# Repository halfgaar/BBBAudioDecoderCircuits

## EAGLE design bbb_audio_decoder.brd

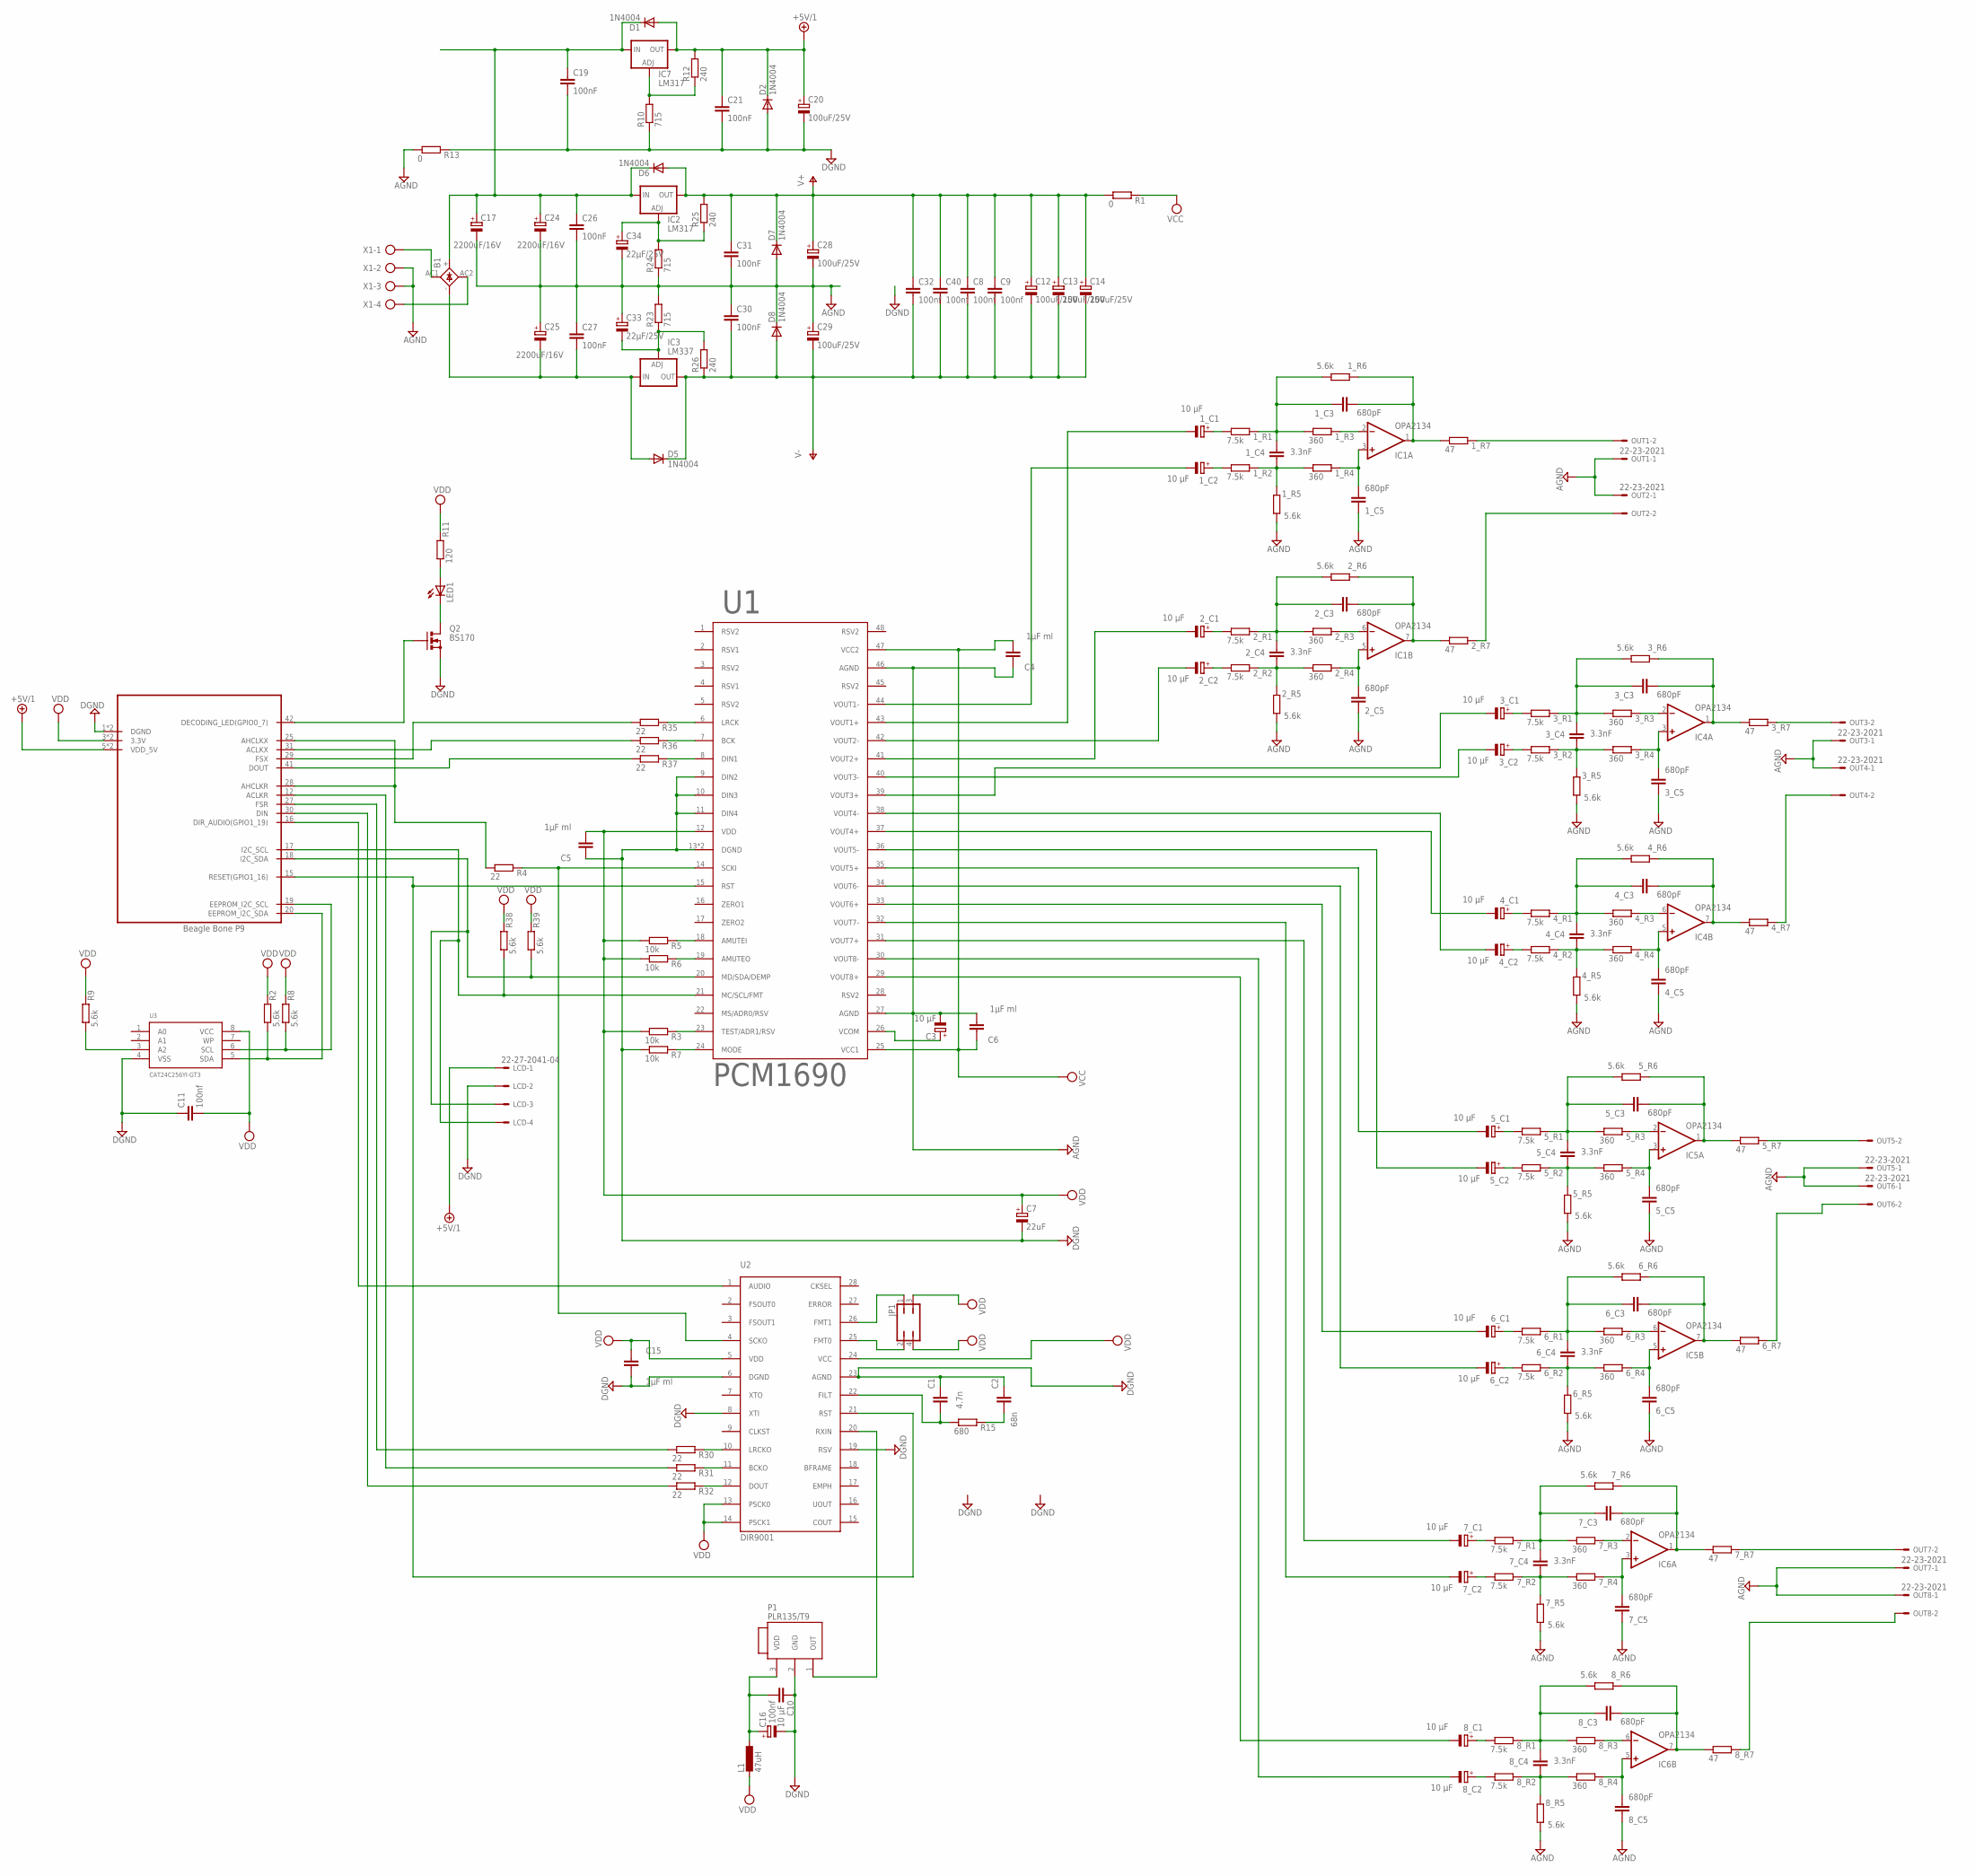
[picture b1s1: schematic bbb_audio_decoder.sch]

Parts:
1_C1, 1_C2, 2_C1, 2_C2, 3_C1, 3_C2, 4_C1, 4_C2, 5_C1, 5_C2, 6_C1, 6_C2, 7_C1, 7_C2, 8_C1, 8_C2: 10 µF; E2-5
1_C3, 1_C5, 2_C3, 2_C5, 3_C3, 3_C5, 4_C3, 4_C5, 5_C3, 5_C5, 6_C3, 6_C5, 7_C3, 7_C5, 8_C3, 8_C5: 680pF; C050-024X044
1_C4, 2_C4, 3_C4, 4_C4, 5_C4, 6_C4, 7_C4, 8_C4: 3.3nF; C050-025X075
1_R1, 1_R2, 2_R1, 2_R2, 3_R1, 3_R2, 4_R1, 4_R2, 5_R1, 5_R2, 6_R1, 6_R2, 7_R1, 7_R2, 8_R1, 8_R2: 7.5k; 0207/7
1_R3, 1_R4, 2_R3, 2_R4, 3_R3, 3_R4, 4_R3, 4_R4, 5_R3, 5_R4, 6_R3, 6_R4, 7_R3, 7_R4, 8_R3, 8_R4: 360; 0207/7
1_R5, 1_R6, 2_R5, 2_R6, 3_R5, 3_R6, 4_R5, 4_R6, 5_R5, 5_R6, 6_R5, 6_R6, 7_R5, 7_R6, 8_R5, 8_R6: 5.6k; 0207/7
1_R7, 2_R7, 3_R7, 4_R7, 5_R7, 6_R7, 7_R7, 8_R7: 47; 0207/7
B1: FB15
C1: 4.7n; C050-024X044
C2: 68n; C050-024X044
C3, C16: 10 µF; E2-5
C4, C5, C6, C15: 1µF ml; C050-024X044
C7: 22uF; E2-5
C8, C9, C10, C11, C32, C40: 100nf; C050-024X044
C12, C13, C14, C20, C28, C29: 100uF/25V; E2,5-6
C17, C24, C25: 2200uF/16V; E5-13
C19, C21, C26, C27, C30, C31: 100nF; C050-024X044
C33, C34: 22µF/25V; E2,5-6
D1, D2, D5, D6, D7, D8: 1N4004; DO41-7.6
IC1, IC4, IC5, IC6: OPA2134; DIL8
IC2, IC7: LM317; 317TS
IC3: LM337; 337TS
JP1: JP2Q
L1: 47uH; 0207/10
LCD: 22-27-2041-04; 6410-04
LED1: LEDSMT1206; 1206
OUT1, OUT2, OUT3, OUT4, OUT5, OUT6, OUT7, OUT8: 22-23-2021
P1: PLR135/T9
Q2: BS170; SOT54E
R1, R13: 0; 0204V
R2, R8, R9, R38, R39: 5.6k; 0207/7
R3, R5, R6, R7: 10k; 0207/7
R4, R30, R31, R32, R35, R36, R37: 22; 0207/7
R10, R23: 715; 0204V
R11: 120; 0204V
R12, R25, R26: 240; 0204V
R15: 680; 0207/7
R24: 715; 0207/10
U1: PCM1690; HTSSOP48DFD
U2: DIR9001; TSSOP28
U3: CAT24C256YI-GT3; TSSOP8
U$1: BEAGLEBONEP9; HEADERS23-2
X1: AK500/4

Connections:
ACLKR: R31.1, U$1.12 (ACLKR)
ACLKX: R36.1, U$1.31 (ACLKX)
AGND: 1_C5.1, 1_R5.1, 2_C5.1, 2_R5.1, 3_C5.1, 3_R5.1, 4_C5.1, 4_R5.1, 5_C5.1, 5_R5.1, 6_C5.1, 6_R5.1, 7_C5.1, 7_R5.1, 8_C5.1, 8_R5.1, C3.-, C4.1, C6.2, C17.-, C24.-, C25.+, C26.2, C27.1, C28.-, C29.+, C30.1, C31.2, C33.+, C34.-, D7.A, D8.C, OUT1.1, OUT2.1, OUT3.1, OUT4.1, OUT5.1, OUT6.1, OUT7.1, OUT8.1, R13.1, R23.2, R24.1, U1.27 (AGND), U1.46 (AGND), X1.2, X1.3
CAPE_I2C_SCL: R8.1, U3.6 (SCL), U$1.19 (EEPROM_I2C_SCL)
CAPE_I2C_SDA: R2.1, U3.5 (SDA), U$1.20 (EEPROM_I2C_SDA)
DGND: C1.1, C2.1, C5.1, C7.-, C10.1, C11.1, C15.2, C16.-, C19.2, C20.-, C21.2, D2.A, LCD.2, P1.2 (GND), Q2.S, R7.1, R10.1, R13.2, U1.9 (DIN2), U1.10 (DIN3), U1.11 (DIN4), U1.13 (DGND), U1.EXP (DGND), U2.6 (DGND), U2.8 (XTI), U2.19 (RSV), U2.23 (AGND), U3.4 (VSS), U$1.1 (DGND), U$1.2 (DGND)
DIN: R32.1, U$1.30 (DIN)
DIR_AUDIO: U2.1 (AUDIO), U$1.16 (DIR_AUDIO(GPIO1_19))
DOUT: R37.1, U$1.41 (DOUT)
FILT: C1.2, R15.1, U2.22 (FILT)
FSR: R30.1, U$1.27 (FSR)
FSX: R35.1, U$1.29 (FSX)
MCLK: R4.1, U$1.25 (AHCLKX), U$1.28 (AHCLKR)
unnamed: B1.AC2, X1.4
unnamed: R3.2, U1.23 (TEST/ADR1/RSV)
unnamed: B1.AC1, X1.1
unnamed: LED1.A, R11.1
unnamed: R4.2, U1.14 (SCKI), U2.4 (SCKO)
unnamed: C2.2, R15.2
unnamed: JP1.2, U2.25 (FMT0)
unnamed: JP1.1, U2.26 (FMT1)
unnamed: 3_C4.1, 3_R2.2, 3_R4.1, 3_R5.2
unnamed: 3_C3.1, 3_C4.2, 3_R1.2, 3_R3.1, 3_R6.1
unnamed: R5.2, U1.18 (AMUTEI)
unnamed: C10.2, C16.+, L1.1, P1.3 (VDD)
unnamed: 1_C4.1, 1_R2.2, 1_R4.1, 1_R5.2
unnamed: 2_C4.1, 2_R2.2, 2_R4.1, 2_R5.2
unnamed: 2_C3.1, 2_C4.2, 2_R1.2, 2_R3.1, 2_R6.1
unnamed: 3_C5.2, 3_R4.2, IC4.3 (+IN)
unnamed: R6.2, U1.19 (AMUTEO)
unnamed: 1_C3.1, 1_C4.2, 1_R1.2, 1_R3.1, 1_R6.1
unnamed: R7.2, U1.24 (MODE)
unnamed: P1.1 (OUT), U2.20 (RXIN)
unnamed: 3_C3.2, 3_R6.2, 3_R7.1, IC4.1 (OUT)
unnamed: 3_R3.2, IC4.2 (-IN)
unnamed: 1_R3.2, IC1.2 (-IN)
unnamed: 1_C5.2, 1_R4.2, IC1.3 (+IN)
unnamed: 1_C2.+, 1_R2.1
unnamed: 1_C3.2, 1_R6.2, 1_R7.1, IC1.1 (OUT)
unnamed: 1_C1.+, 1_R1.1
unnamed: LED1.C, Q2.D
unnamed: 7_C4.1, 7_R2.2, 7_R4.1, 7_R5.2
unnamed: 2_C5.2, 2_R4.2, IC1.5 (+IN)
unnamed: 2_C3.2, 2_R6.2, 2_R7.1, IC1.7 (OUT)
unnamed: 2_R3.2, IC1.6 (-IN)
unnamed: 2_C2.+, 2_R2.1
unnamed: 2_C1.+, 2_R1.1
unnamed: 7_C3.1, 7_C4.2, 7_R1.2, 7_R3.1, 7_R6.1
unnamed: 7_C5.2, 7_R4.2, IC6.3 (+IN)
unnamed: 1_R7.2, OUT1.2
unnamed: 2_R7.2, OUT2.2
unnamed: B1.+, C17.+, C19.1, C24.+, C26.1, D1.C, D6.C, IC2.3 (IN), IC7.3 (IN)
unnamed: IC7.1 (ADJ), R10.2, R12.1
unnamed: B1.-, C25.-, C27.2, D5.A, IC3.2 (IN)
unnamed: C33.-, IC3.1 (ADJ), R23.1, R26.2
unnamed: C34.+, IC2.1 (ADJ), R24.2, R25.1
unnamed: 3_C2.+, 3_R2.1
unnamed: 3_C1.+, 3_R1.1
unnamed: 7_C3.2, 7_R6.2, 7_R7.1, IC6.1 (OUT)
unnamed: 7_R3.2, IC6.2 (-IN)
unnamed: 4_C4.1, 4_R2.2, 4_R4.1, 4_R5.2
unnamed: 4_C3.1, 4_C4.2, 4_R1.2, 4_R3.1, 4_R6.1
unnamed: 4_C5.2, 4_R4.2, IC4.5 (+IN)
unnamed: R32.2, U2.12 (DOUT)
unnamed: R31.2, U2.11 (BCKO)
unnamed: R30.2, U2.10 (LRCKO)
unnamed: R9.1, U3.3 (A2)
unnamed: 4_C3.2, 4_R6.2, 4_R7.1, IC4.7 (OUT)
unnamed: 4_R3.2, IC4.6 (-IN)
unnamed: 4_C2.+, 4_R2.1
unnamed: 4_C1.+, 4_R1.1
unnamed: 7_C2.+, 7_R2.1
unnamed: 7_C1.+, 7_R1.1
unnamed: R37.2, U1.8 (DIN1)
unnamed: R36.2, U1.7 (BCK)
unnamed: R35.2, U1.6 (LRCK)
unnamed: 3_R7.2, OUT3.2
unnamed: 4_R7.2, OUT4.2
unnamed: 5_C4.1, 5_R2.2, 5_R4.1, 5_R5.2
unnamed: 5_C3.1, 5_C4.2, 5_R1.2, 5_R3.1, 5_R6.1
unnamed: 5_C5.2, 5_R4.2, IC5.3 (+IN)
unnamed: 5_C3.2, 5_R6.2, 5_R7.1, IC5.1 (OUT)
unnamed: 5_R3.2, IC5.2 (-IN)
unnamed: 5_C2.+, 5_R2.1
unnamed: 5_C1.+, 5_R1.1
unnamed: 8_C4.1, 8_R2.2, 8_R4.1, 8_R5.2
unnamed: 8_C3.1, 8_C4.2, 8_R1.2, 8_R3.1, 8_R6.1
unnamed: 6_C4.1, 6_R2.2, 6_R4.1, 6_R5.2
unnamed: 6_C3.1, 6_C4.2, 6_R1.2, 6_R3.1, 6_R6.1
unnamed: 6_C5.2, 6_R4.2, IC5.5 (+IN)
unnamed: 6_C3.2, 6_R6.2, 6_R7.1, IC5.7 (OUT)
unnamed: 6_R3.2, IC5.6 (-IN)
unnamed: 6_C2.+, 6_R2.1
unnamed: 6_C1.+, 6_R1.1
unnamed: 5_R7.2, OUT5.2
unnamed: 6_R7.2, OUT6.2
unnamed: 8_C5.2, 8_R4.2, IC6.5 (+IN)
unnamed: 8_C3.2, 8_R6.2, 8_R7.1, IC6.7 (OUT)
unnamed: 8_R3.2, IC6.6 (-IN)
unnamed: 8_C2.+, 8_R2.1
unnamed: 8_C1.+, 8_R1.1
unnamed: 7_R7.2, OUT7.2
unnamed: 8_R7.2, OUT8.2
unnamed: Q2.G, U$1.42 (DECODING_LED(GPIO0_7))
RST: U1.15 (RST), U2.21 (RST), U$1.15 (RESET(GPIO1_16))
SCL: LCD.4, R38.1, U1.21 (MC/SCL/FMT), U$1.17 (I2C_SCL)
SDA: LCD.3, R39.1, U1.20 (MD/SDA/DEMP), U$1.18 (I2C_SDA)
V+: C8.1, C9.1, C12.+, C13.+, C14.+, C28.+, C31.1, C32.1, C40.1, D6.A, D7.C, IC1.8 (V+), IC2.2 (OUT), IC4.8 (V+), IC5.8 (V+), IC6.8 (V+), R1.1, R25.2
V-: C8.2, C9.2, C12.-, C13.-, C14.-, C29.-, C30.2, C32.2, C40.2, D5.C, D8.A, IC1.4 (V-), IC3.3 (OUT), IC4.4 (V-), IC5.4 (V-), IC6.4 (V-), R26.1
VCC: C4.2, C6.1, R1.2, U1.25 (VCC1), U1.47 (VCC2)
VCOM: C3.+, U1.26 (VCOM)
VDD: C5.2, C7.+, C11.2, C15.1, JP1.3, JP1.4, L1.2, R2.2, R3.1, R5.1, R6.1, R8.2, R9.2, R11.2, R38.2, R39.2, U1.12 (VDD), U2.5 (VDD), U2.13 (PSCK0), U2.14 (PSCK1), U2.24 (VCC), U3.8 (VCC), U$1.3 (3.3V), U$1.4 (3.3V)
VDD_5V: C20.+, C21.1, D1.A, D2.C, IC7.2 (OUT), LCD.1, R12.2, U$1.5 (VDD_5V), U$1.6 (VDD_5V)
VOUT1+: 1_C1.-, U1.43 (VOUT1+)
VOUT1-: 1_C2.-, U1.44 (VOUT1-)
VOUT2+: 2_C1.-, U1.41 (VOUT2+)
VOUT2-: 2_C2.-, U1.42 (VOUT2-)
VOUT3+: 3_C1.-, U1.39 (VOUT3+)
VOUT3-: 3_C2.-, U1.40 (VOUT3-)
VOUT4+: 4_C1.-, U1.37 (VOUT4+)
VOUT4-: 4_C2.-, U1.38 (VOUT4-)
VOUT5+: 5_C1.-, U1.35 (VOUT5+)
VOUT5-: 5_C2.-, U1.36 (VOUT5-)
VOUT6+: 6_C1.-, U1.33 (VOUT6+)
VOUT6-: 6_C2.-, U1.34 (VOUT6-)
VOUT7+: 7_C1.-, U1.31 (VOUT7+)
VOUT7-: 7_C2.-, U1.32 (VOUT7-)
VOUT8+: 8_C1.-, U1.29 (VOUT8+)
VOUT8-: 8_C2.-, U1.30 (VOUT8-)

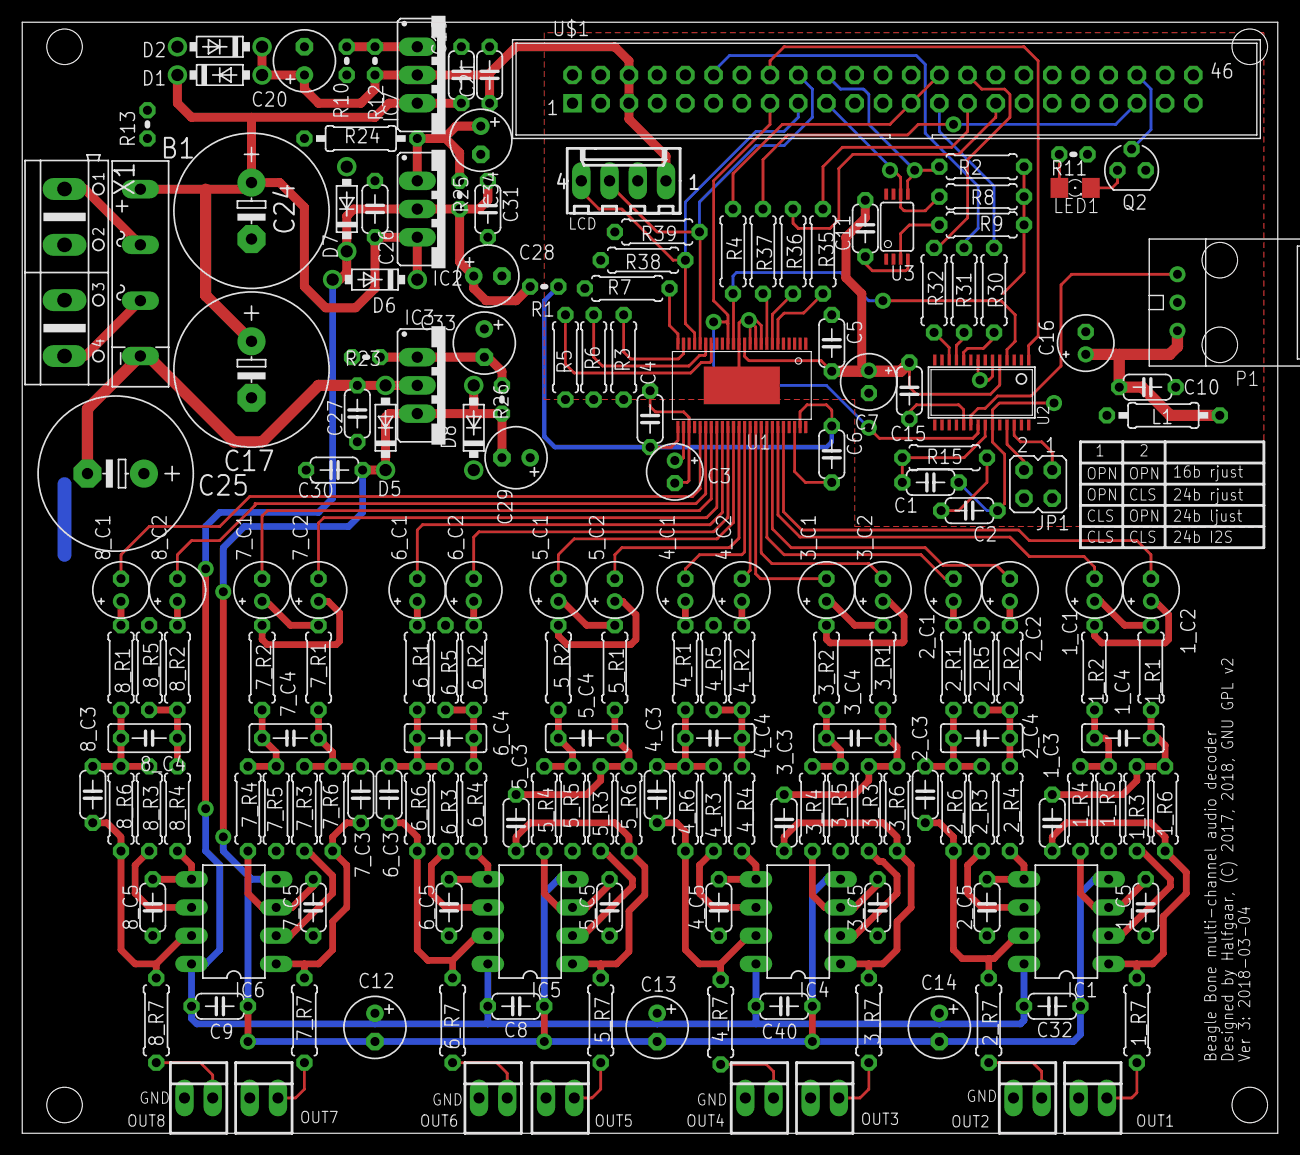
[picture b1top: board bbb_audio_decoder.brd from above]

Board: 2 copper layers, 113.0 x 100.0 mm, 187 parts (0 on the bottom side), 129 nets.

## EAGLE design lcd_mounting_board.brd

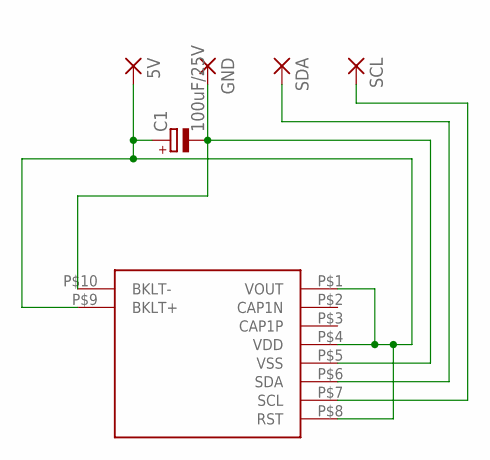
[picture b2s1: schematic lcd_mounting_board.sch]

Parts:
5V: 2,15/1,0
C1: 100uF/25V; E2,5-6
GND: 2,15/1,0
SCL: 2,15/1,0
SDA: 2,15/1,0
U$1: MCCOG22005A6W-BNMLWI

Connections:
5V: 5V.1, C1.+, U$1.P$1 (VOUT), U$1.P$4 (VDD), U$1.P$8 (RST), U$1.P$9 (BKLT+)
GND: C1.-, GND.1, U$1.P$5 (VSS), U$1.P$10 (BKLT-)
SCL: SCL.1, U$1.P$7 (SCL)
SDA: SDA.1, U$1.P$6 (SDA)

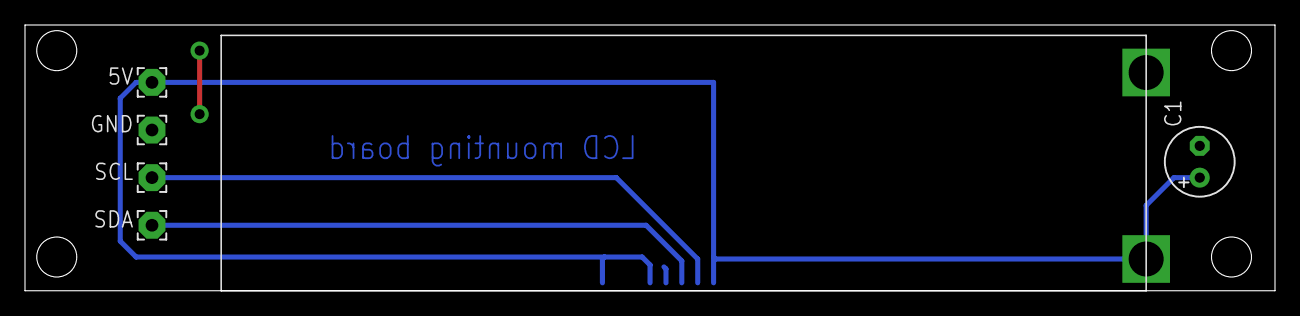
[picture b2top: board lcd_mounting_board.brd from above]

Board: 2 copper layers, 100.0 x 21.3 mm, 6 parts (0 on the bottom side), 4 nets.

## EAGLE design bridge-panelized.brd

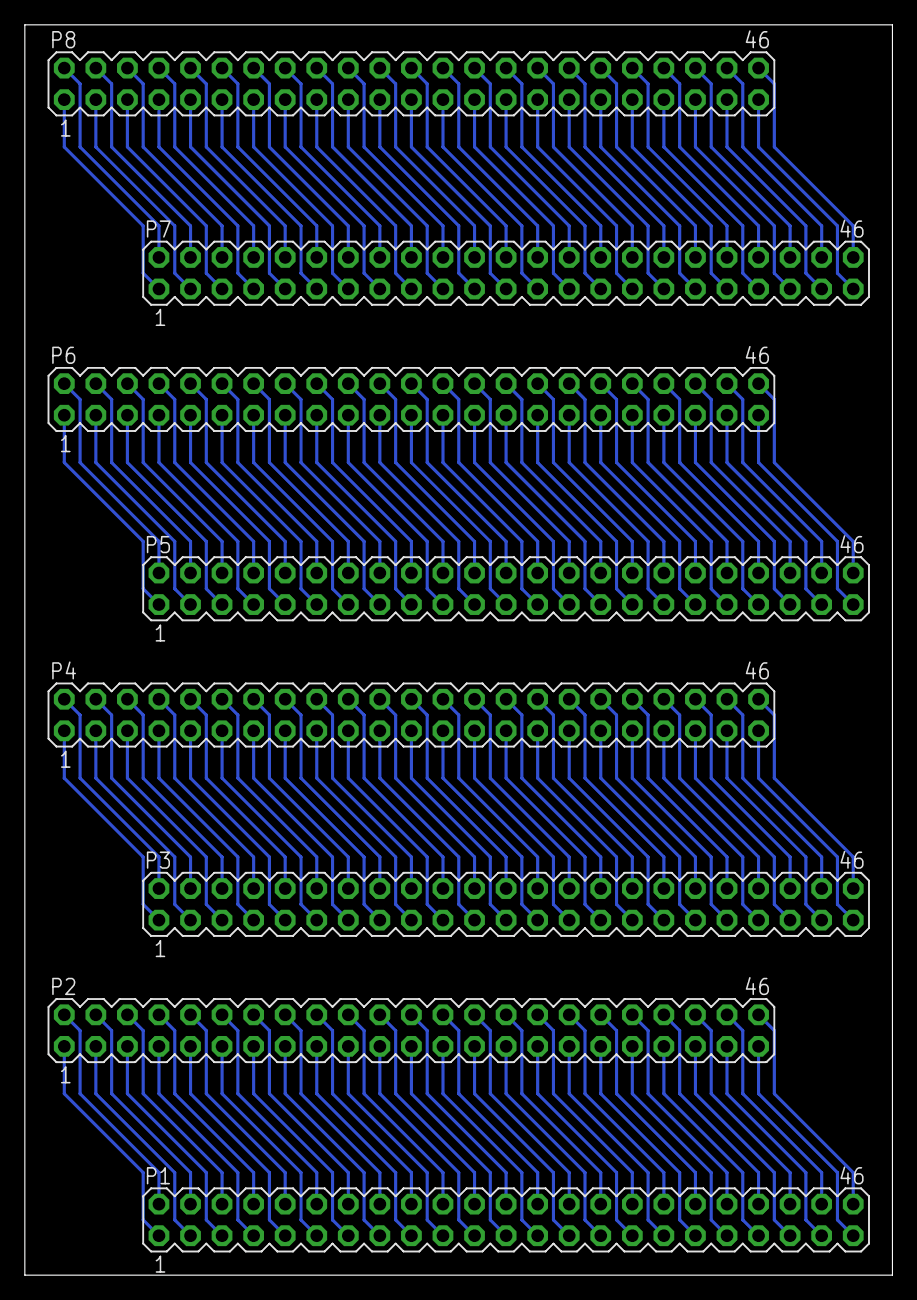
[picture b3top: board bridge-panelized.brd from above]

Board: 2 copper layers, 69.8 x 100.6 mm, 8 parts (0 on the bottom side), 184 nets.

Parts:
P1, P2, P3, P4, P5, P6, P7, P8: HEADERS23-2; MA23-2

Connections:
unnamed: P1.1, P2.1
unnamed: P1.3, P2.3
unnamed: P1.5, P2.5
unnamed: P1.7, P2.7
unnamed: P1.9, P2.9
unnamed: P1.11, P2.11
unnamed: P1.13, P2.13
unnamed: P1.15, P2.15
unnamed: P1.17, P2.17
unnamed: P1.19, P2.19
unnamed: P1.21, P2.21
unnamed: P1.23, P2.23
unnamed: P1.25, P2.25
unnamed: P1.27, P2.27
unnamed: P1.29, P2.29
unnamed: P1.31, P2.31
unnamed: P1.33, P2.33
unnamed: P1.35, P2.35
unnamed: P1.37, P2.37
unnamed: P1.39, P2.39
unnamed: P1.41, P2.41
unnamed: P1.43, P2.43
unnamed: P1.45, P2.45
unnamed: P1.2, P2.2
unnamed: P1.4, P2.4
unnamed: P1.6, P2.6
unnamed: P1.8, P2.8
unnamed: P1.10, P2.10
unnamed: P1.12, P2.12
unnamed: P1.14, P2.14
unnamed: P1.16, P2.16
unnamed: P1.18, P2.18
unnamed: P1.20, P2.20
unnamed: P1.22, P2.22
unnamed: P1.24, P2.24
unnamed: P1.26, P2.26
unnamed: P1.28, P2.28
unnamed: P1.30, P2.30
unnamed: P1.32, P2.32
unnamed: P1.34, P2.34
unnamed: P1.36, P2.36
unnamed: P1.38, P2.38
unnamed: P1.40, P2.40
unnamed: P1.42, P2.42
unnamed: P1.44, P2.44
unnamed: P1.46, P2.46
unnamed: P3.1, P4.1
unnamed: P3.3, P4.3
unnamed: P3.5, P4.5
unnamed: P3.7, P4.7
unnamed: P3.9, P4.9
unnamed: P3.11, P4.11
unnamed: P3.13, P4.13
unnamed: P3.15, P4.15
unnamed: P3.17, P4.17
unnamed: P3.19, P4.19
unnamed: P3.21, P4.21
unnamed: P3.23, P4.23
unnamed: P3.25, P4.25
unnamed: P3.27, P4.27
unnamed: P3.29, P4.29
unnamed: P3.31, P4.31
unnamed: P3.33, P4.33
unnamed: P3.35, P4.35
unnamed: P3.37, P4.37
unnamed: P3.39, P4.39
unnamed: P3.41, P4.41
unnamed: P3.43, P4.43
unnamed: P3.45, P4.45
unnamed: P3.2, P4.2
unnamed: P3.4, P4.4
unnamed: P3.6, P4.6
unnamed: P3.8, P4.8
unnamed: P3.10, P4.10
unnamed: P3.12, P4.12
unnamed: P3.14, P4.14
unnamed: P3.16, P4.16
unnamed: P3.18, P4.18
unnamed: P3.20, P4.20
unnamed: P3.22, P4.22
unnamed: P3.24, P4.24
unnamed: P3.26, P4.26
unnamed: P3.28, P4.28
unnamed: P3.30, P4.30
unnamed: P3.32, P4.32
unnamed: P3.34, P4.34
unnamed: P3.36, P4.36
unnamed: P3.38, P4.38
unnamed: P3.40, P4.40
unnamed: P3.42, P4.42
unnamed: P3.44, P4.44
unnamed: P3.46, P4.46
unnamed: P5.1, P6.1
unnamed: P5.3, P6.3
unnamed: P5.5, P6.5
unnamed: P5.7, P6.7
unnamed: P5.9, P6.9
unnamed: P5.11, P6.11
unnamed: P5.13, P6.13
unnamed: P5.15, P6.15
unnamed: P5.17, P6.17
unnamed: P5.19, P6.19
unnamed: P5.21, P6.21
unnamed: P5.23, P6.23
unnamed: P5.25, P6.25
unnamed: P5.27, P6.27
unnamed: P5.29, P6.29
unnamed: P5.31, P6.31
unnamed: P5.33, P6.33
unnamed: P5.35, P6.35
unnamed: P5.37, P6.37
unnamed: P5.39, P6.39
unnamed: P5.41, P6.41
unnamed: P5.43, P6.43
unnamed: P5.45, P6.45
unnamed: P5.2, P6.2
unnamed: P5.4, P6.4
unnamed: P5.6, P6.6
unnamed: P5.8, P6.8
unnamed: P5.10, P6.10
unnamed: P5.12, P6.12
unnamed: P5.14, P6.14
unnamed: P5.16, P6.16
unnamed: P5.18, P6.18
unnamed: P5.20, P6.20
unnamed: P5.22, P6.22
unnamed: P5.24, P6.24
unnamed: P5.26, P6.26
unnamed: P5.28, P6.28
unnamed: P5.30, P6.30
unnamed: P5.32, P6.32
unnamed: P5.34, P6.34
unnamed: P5.36, P6.36
unnamed: P5.38, P6.38
unnamed: P5.40, P6.40
unnamed: P5.42, P6.42
unnamed: P5.44, P6.44
unnamed: P5.46, P6.46
unnamed: P7.1, P8.1
unnamed: P7.3, P8.3
unnamed: P7.5, P8.5
unnamed: P7.7, P8.7
unnamed: P7.9, P8.9
unnamed: P7.11, P8.11
unnamed: P7.13, P8.13
unnamed: P7.15, P8.15
unnamed: P7.17, P8.17
unnamed: P7.19, P8.19
unnamed: P7.21, P8.21
unnamed: P7.23, P8.23
unnamed: P7.25, P8.25
unnamed: P7.27, P8.27
unnamed: P7.29, P8.29
unnamed: P7.31, P8.31
unnamed: P7.33, P8.33
unnamed: P7.35, P8.35
unnamed: P7.37, P8.37
unnamed: P7.39, P8.39
unnamed: P7.41, P8.41
unnamed: P7.43, P8.43
unnamed: P7.45, P8.45
unnamed: P7.2, P8.2
unnamed: P7.4, P8.4
unnamed: P7.6, P8.6
unnamed: P7.8, P8.8
unnamed: P7.10, P8.10
unnamed: P7.12, P8.12
unnamed: P7.14, P8.14
unnamed: P7.16, P8.16
unnamed: P7.18, P8.18
unnamed: P7.20, P8.20
unnamed: P7.22, P8.22
unnamed: P7.24, P8.24
unnamed: P7.26, P8.26
unnamed: P7.28, P8.28
unnamed: P7.30, P8.30
unnamed: P7.32, P8.32
unnamed: P7.34, P8.34
unnamed: P7.36, P8.36
unnamed: P7.38, P8.38
unnamed: P7.40, P8.40
unnamed: P7.42, P8.42
unnamed: P7.44, P8.44
unnamed: P7.46, P8.46

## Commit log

2015-06-04 Progressing nicely. Time for a first commit.
2017-01-01 Ignores
2017-01-16 Taking the Beaglebone approach
2017-01-22 Reversed opamp
    Because signals are now on top layer, the layout had to be mirrored.
2017-01-22 Copied two extra output stages
2017-01-22 Added another analog output stage
2017-01-22 Added the last analog output stage
2017-01-27 Working on EEPROM and TOSLINK
2017-01-28 Mostly the analog section, routing and squeezing
2017-01-29 Rotated PSU section, and more work since
2017-01-30 stuff
2017-02-02 ignore file
2017-02-02 Very nearly done
    I added some power and ground planes and finished more routing.
    Still a bit of decision making to do before I can finish it.
2017-02-02 Fixed 5mm caps, fixed DRC errors
2017-02-06 Added bridge
2017-02-06 Added screw holes
2017-02-06 Some moving around for DRC and one tiny airwire
2017-02-06 Approved errors and fixed DIR9001 PIN bug
2017-02-06 Fixed DIR9001 VCC 3.3V misunderstanding
    VCC is actually 3.3V, and AGND is only different from GND in where the
    FILT ties. Almost have that complete. Need to tie the AGND to DGND
    first, and not at a common point with the filter.
2017-02-07 Gave FILT on DIR9001 a dedicated gnd
2017-02-07 Removed unnecessary decoupling cap
    I had added it to decouple VCC to DIR9001, but it didn't even need VCC,
    that was a bug.
2017-02-07 Fixed bug in joining VCC and V+
    I now use a 0 Ohm resistor to join VCC and V+. The jumper is also fixed,
    because I had erroneously tied the PCM1690 VCC to VDD_5V on the beagle
    bone, which means the beagle bone's adapter would have powered the
    PCM1690.
2017-02-07 Removed unnecessary vias
    By moving a bit of wire, the VDD plane is now more continuous.
2017-02-08 Added two status LEDs
2017-02-08 Molex output connectors
2017-02-08 Jumper info on silkscreen
2017-02-08 SCKO selection jumper removed: unneeded
2017-02-08 Version and author info
2017-02-08 Approve more ERC stuff
2017-02-08 Use CAT24C256 with named package suffix
2017-02-09 Changed opamp to value OPA2134
2017-02-09 One more decoupling cap
2017-02-09 Renamed
2017-02-09 Wrote version on board
2017-02-19 Made gebers of ver1
    (and snuck in a component value change, because it was a bug and is still
    part of ver1)
2017-02-19 Renamed 5.5 mm adapter symbol
    This one specifies the inner diameter too.
2017-02-19 Use updated PCM1690 package
    Description was wrong, and the thermal pad wasn't connected.
2017-02-19 Offset bridge connector
    This is necessary if I want to put the TOSLINK connector right through
    the chassis.
2017-02-19 Moved C3 and C4 a bit apart
2017-02-27 Moved tnames to more legible place
2017-02-28 Move the top row of the bridge down a bit
    This makes it fit four times in 10 cm.
    Also made a panelized version of the board.
2017-03-03 Mirrored the offset of the bridge connector
    I made a very stupid mistake and offset it the wrong direction. I
    thought I accounted for the board being upside-down, but I messed up...
    Hours of work down the drain.
2017-05-30 Fix DIR9001 DOUT wrong connection
    It was wired to pin 32 in BBB P9, which is VADC. The correct pin is 30.
2017-06-25 Fixes wrong net name
2017-07-24 Use P9 connector with wiring for slave m-clock
    As described from the eaglecustom repo:
    > For my purpose, I need to use an external master clock. This is input on
    > ahclkr, which is pin 28. For that, the previous pin 28 function, axr2,
    > has been moved to axr1, pin 41. And for that, the 'ready' LED that was
    > on pin 41 has been removed.
2017-07-25 Set DIR9001 SCKO to 512 * Fs
    Both PSCKO pins connect to VDD. I need this to drive 8 channel TDM mode
    in the mcasp in the Beagle Bone.
2017-09-24 DIR9001 SCKO goes to input of PCM1690 and BBB
    This follows commit c6b4b11003516838945a68f4a9d2063d0b8848d0; we now
    actually connect the master clock.
2017-10-29 Included LM317 voltage regulator for Beagle Bone
    This is the power supply for it, removing the need for a power adapter
    for it.
    This also changes the AC input to needing a dual winding transformer. My
    idea of univeral adapters was nice, until AC "wall warts" became illegal
    because of energy laws... Plus, I reduced the supply caps, so I need the
    full-wave rectifier now.
2017-11-02 Added molex 22-27-2041 connector for LCD
2017-11-02 Replaced LED with 1206 SMD one
2017-11-04 Added LCD mounting board
2017-11-04 Add ground plane to bridge
    This creates nice 50 Ohm impedance transmission lines (ish).
2017-11-04 Added gerbers for ver2
    Also made one final change: a bit of polygon restrict around the screw
    holes, to avoid accendital contact to chassis.
2017-11-06 LCD board, moved everything up a bit, for PCB cutting
2018-02-03 Connect DIR9001 SCKO to AHCLKR as well.
    This is a follow-up of commit c6b4b11, where I apparently only connected
    the recovered clock from the DIR9001 to AHCLKX.
2018-03-04 Separate AGND plane in two, to avoid hum
    The one large ground plane seemed to cause the charging current for the
    main filter caps to circulate around the entire plane, causing the
    signal output ground and circuit ground reference to have different
    potentials, causing a 100 Hz max hum of -75dBV on some outputs.
    This fix breaks the ground plane in two and connects them together with
    a small track, to keep the circuit ground clear of those charging
2018-03-04 GPLv2 license
2018-03-04 Version 3
    Gerbers and an update to version number on the silkscreen.
2020-10-17 TODO file
2020-10-24 Add another power supply cap to fix boot problems
    The extra cap (C17) is 2200µF.
    The problem was that it sometimes refused to boot. I saw the
    BeagleBone's blue lights go off again when the boot process was
    initiated. The LCD backlight dipped. Scope image revealved dips in the
    rail, together with 100Hz rectification ripple. As a hack to my build, I
    added 4700µF before the positive regulators. That prevented the

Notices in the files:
bbb_audio_decoder.brd:
Designed by Halfgaar, (C) 2017, 2018, GNU GPL v2
